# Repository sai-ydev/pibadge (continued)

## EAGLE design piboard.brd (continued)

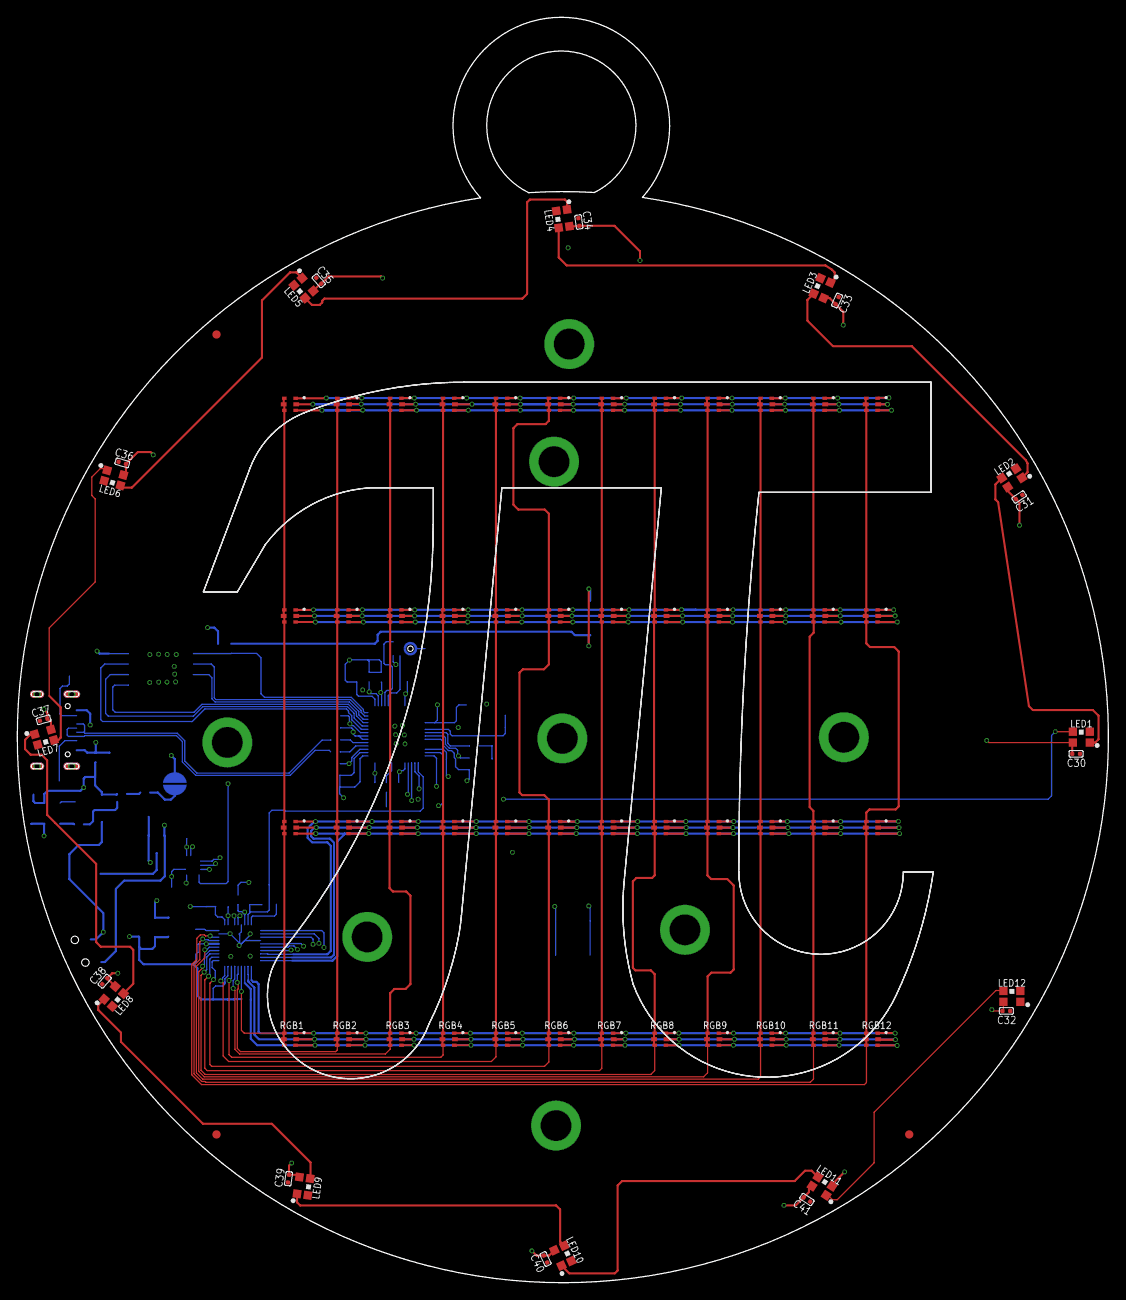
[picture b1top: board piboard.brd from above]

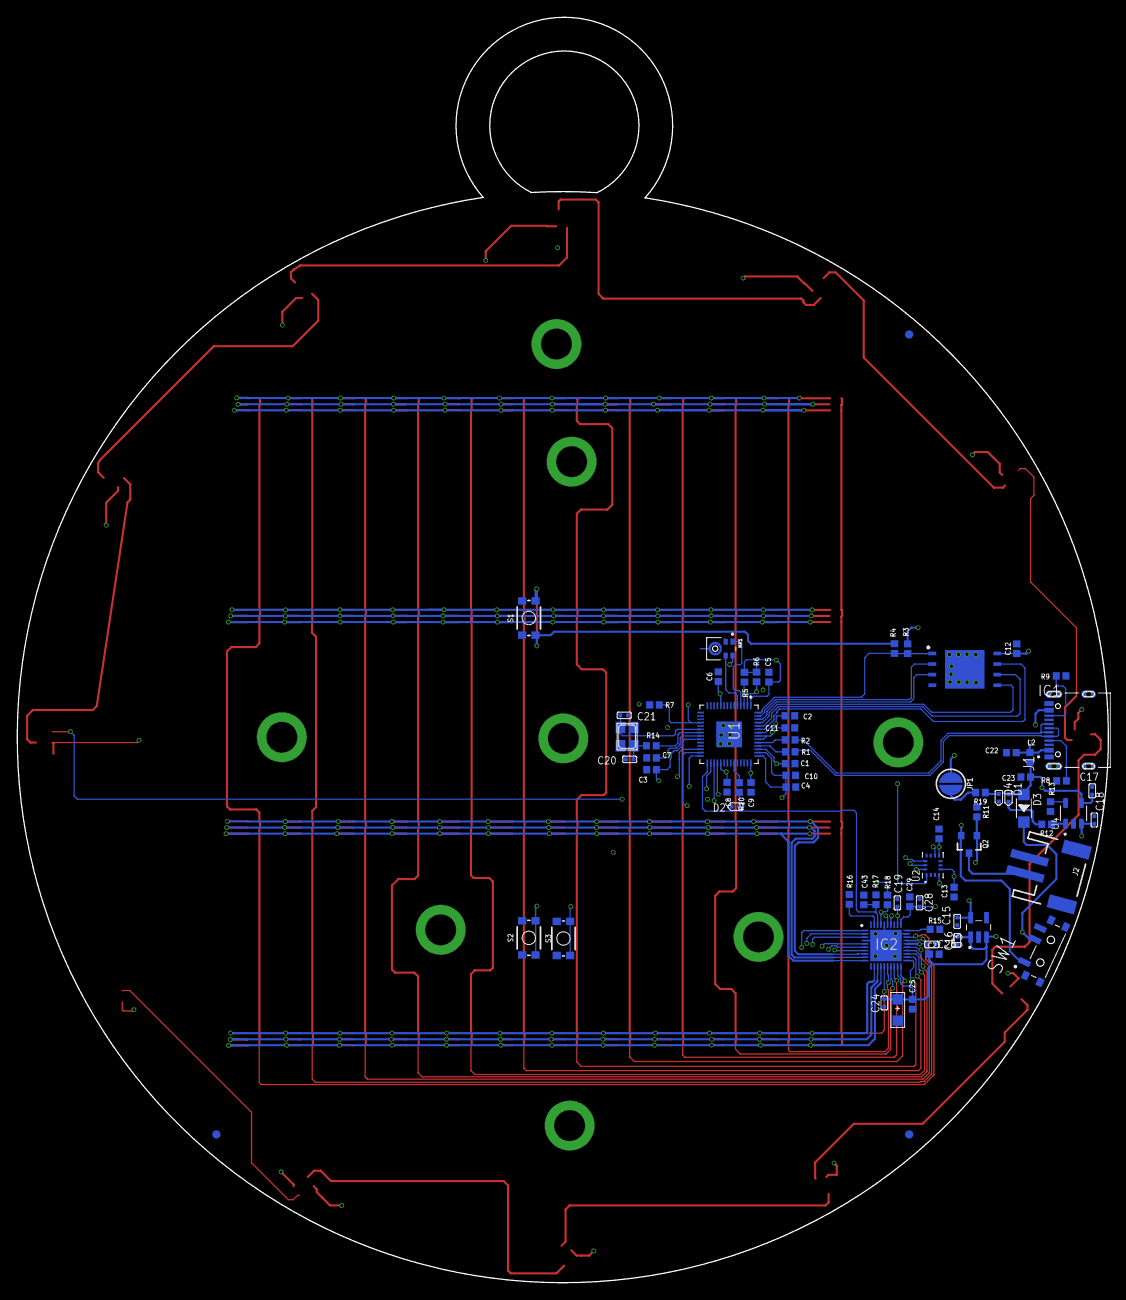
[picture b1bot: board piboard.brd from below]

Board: 4 copper layers, 131.0 x 151.9 mm, 157 parts (74 on the bottom side), 80 nets.

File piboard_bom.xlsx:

Comment | Designator | Footprint | LCSC Part #
LiPo Battery Connector | J2 | 1x2P | C295747
12MHz | Q1 | SMD3225-4P | C654952
1K | R14 | 402 | C3015791
0.1uF | C1 C2 C5 C6 C7 C8 C9 C10 C11 C12 C13 C14 C22 C23 C25 C27 C29 C43 | 402 | C141382
1.0uF | C3 C4 | 402 | C968773
2.2nH | L2 | 402 | C370207
2.5A/30V/105mÎ© | Q2 | SOT23-3 | C5182052
2K | R13 | 402 | C5140070
4.7K | R5 R6 | 402 | C3152117
4.7uF | C17 C18 | C0402 | C5157687
5.1K | R8 R9 | 402 | C325521
10K | R3 R4 R7 R11 | 402 | C3015825
10uF | C15 C16 | C0402 | C2846677
20K | R15 | 402 | C3015841
20V-1A | D3 | SOD-123 | C5204747
22uF | C42 | AVX-A | C11366
27 | R1 R2 | 402 | C3017455
30pf | C20 C21 | C0402 | C5182450
100K | R16 R17 R18 | 402 | C3015887
220 | R19 | 402 | C3017470
330 | R10 | 402 | C3015774
470 | R12 | 402 | C3015779
470nF 50V | C19 C24 C26 C28 | C0402 | C967572
BLUE-0402 | D1 D2 | LED-0402 | C130724
BMI270 | U2 | XDCR_BMI270 | C2836813
FIDUCIAL1X2 | FD2 FD4 FD6 | FIDUCIAL-1X2 | DNF
ICS-41350 | MK1 | MIC_ICS-41350 | C2895290
IS25LP256D-JLLE-TR | IC1 | SON127P800X600X80-9N | C2886434
IS31FL3737-QFLS4-TR | IC2 | QFN40P500X500X80-41N | C506254
JUMPER-SMT_2_NO_SILK_ROUND | JP1 | SMT-JUMPER_2_NO_SILK_ROUND | DNF
MCP73831T-2ATI/OT | U4 | SOT95P280X145-5N | C14879
MIC5504-3.3YM5_TR | U3 | SOT95P280X145-5N | C3021093
MOMENTARY-SWITCH-SPST-SMD-4.6X2.8MM | S1 S2 S3 | TACTILE_SWITCH_SMD_4.6X2.8MM | C99271
PCM12SMTR | SW1 | SW_PCM12SMTR | C221841
RED-0402 | D4 | LED-0402 | C130719
RP2040 | U1 | QFN40P700X700X90-57N | C2040
TYPE-C-31-M-12 | J1 | HRO_TYPE-C-31-M-12 | C165948
19-337C/RSBHGHC-A88/4T | RGB1 RGB2 RGB3 RGB4 RGB5 RGB6 RGB7 RGB8 RGB9 RGB10 RGB11 RGB12 RGB13 RGB14 RGB1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 | LED_19-337C/RSBHGHC-A88/4T | C3019536
100nf | C30 C31 C32 C33 C34 C35 C36 C37 C38 C39 C40 C41 | C0402 | C141382
FIDUCIAL1X2 | FD1 FD3 FD5 | FIDUCIAL-1X2 | DNF
WS2812B-2020 | LED1 LED2 LED3 LED4 LED5 LED6 LED7 LED8 LED9 LED10 LED11 LED12 | WS2812B-2020 | C965555

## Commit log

2023-02-08 board files check-in
2023-02-09 Daily check-in
2023-02-13 Board check-in
2023-02-25 Arduino sketch
